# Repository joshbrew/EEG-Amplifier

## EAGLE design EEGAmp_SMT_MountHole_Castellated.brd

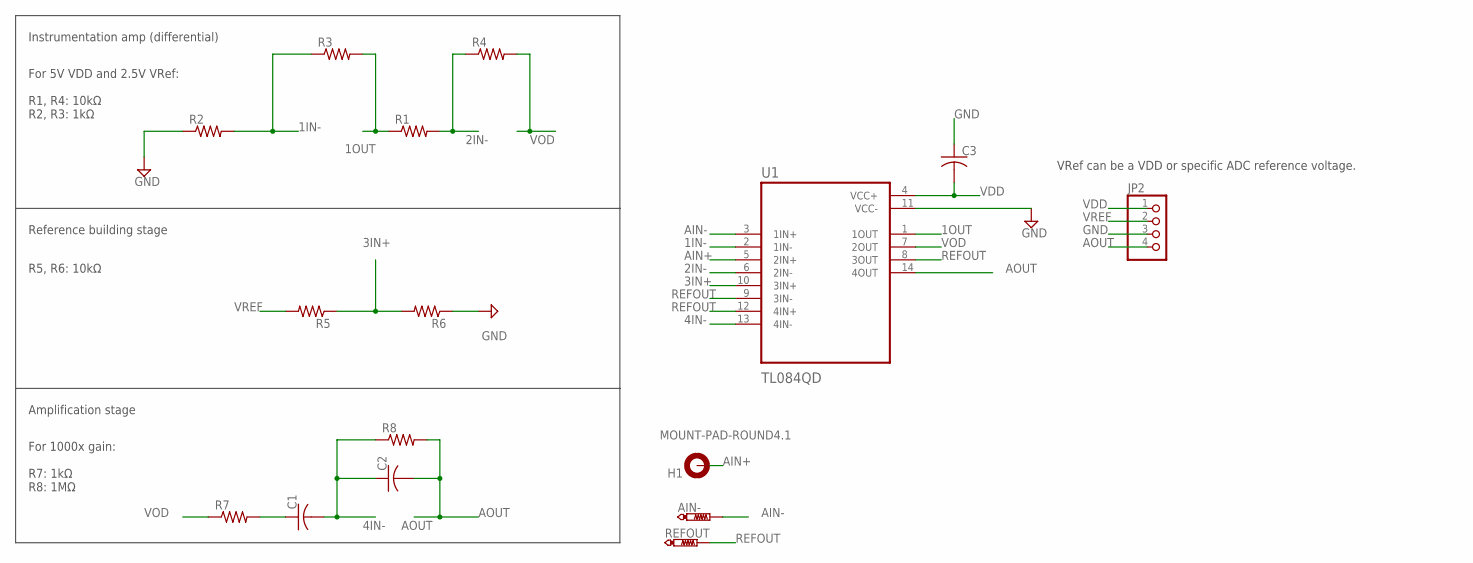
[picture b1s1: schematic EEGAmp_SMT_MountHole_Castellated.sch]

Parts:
AIN-: PTR1PAD1-17; P1-17
C1, C2, C3: C-USC0402; C0402
H1: MOUNT-PAD-ROUND4.1; 4,1-PAD
JP2: PINHD-1X4; 1X04
R1, R2, R3, R4, R5, R6, R7, R8: R-US_R0402; R0402
REFOUT: PTR1PAD1-17; P1-17
U1: TL084QD; SOIC127P600X175-14N

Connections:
1IN-: R2.2, R3.1, U1.2 (1IN-)
1OUT: R1.1, R3.2, U1.1 (1OUT)
2IN-: R1.2, R4.1, U1.6 (2IN-)
3IN+: R5.1, R6.2, U1.10 (3IN+)
4IN-: C1.2, C2.1, R8.1, U1.13 (4IN-)
AIN+: H1.B4,1, U1.5 (2IN+)
AIN-: AIN-.TP, U1.3 (1IN+)
AOUT: C2.2, JP2.4, R8.2, U1.14 (4OUT)
GND: C3.1, JP2.3, R2.1, R6.1, U1.11 (VCC-)
unnamed: C1.1, R7.2
REFOUT: REFOUT.TP, U1.8 (3OUT), U1.9 (3IN-), U1.12 (4IN+)
VDD: C3.2, JP2.1, U1.4 (VCC+)
VOD: R4.2, R7.1, U1.7 (2OUT)
VREF: JP2.2, R5.2

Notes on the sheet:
Instrumentation amp (differential)
Reference building stage
Amplification stage
For 5V VDD and 2.5V VRef: R1, R4: 10kΩ R2, R3: 1kΩ
R5, R6: 10kΩ
For 1000x gain: R7: 1kΩ R8: 1MΩ
VRef can be a VDD or specific ADC reference voltage.

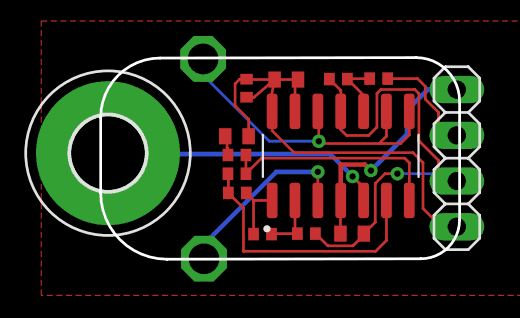
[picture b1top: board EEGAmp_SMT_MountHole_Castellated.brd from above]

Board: 2 copper layers, 19.9 x 11.2 mm, 16 parts (0 on the bottom side), 14 nets.

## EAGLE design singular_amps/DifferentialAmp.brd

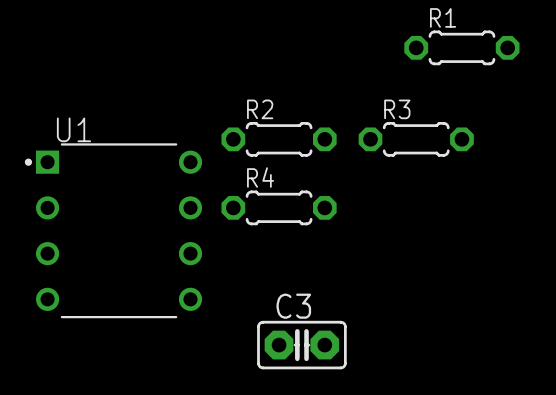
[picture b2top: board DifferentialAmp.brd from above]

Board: 2 copper layers, 6 parts (0 on the bottom side), 5 nets, no tracks yet.

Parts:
C3: C2.5-2
R1, R2, R3, R4: 0204/5
U1: TL082CP; DIP794W45P254L959H508Q8

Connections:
1IN-: R2.2, R3.1, U1.5
1OUT: R1.1, R3.2, U1.1
2IN-: R1.2, R4.1, U1.6
GND: C3.1, R2.1
VOD: R4.2, U1.7

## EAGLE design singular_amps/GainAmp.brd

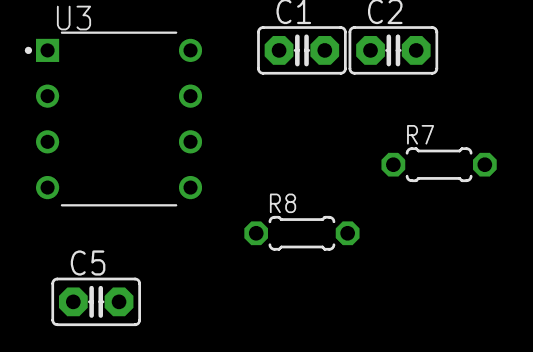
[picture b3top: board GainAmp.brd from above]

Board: 2 copper layers, 6 parts (0 on the bottom side), 3 nets, no tracks yet.

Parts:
C1, C2, C5: C2.5-2
R7, R8: 0204/5
U3: TL081CP; DIP794W45P254L959H508Q8

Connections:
4IN-: C1.2, C2.1, R8.1, U3.2
AOUT: C2.2, R8.2, U3.6
unnamed: C1.1, R7.2

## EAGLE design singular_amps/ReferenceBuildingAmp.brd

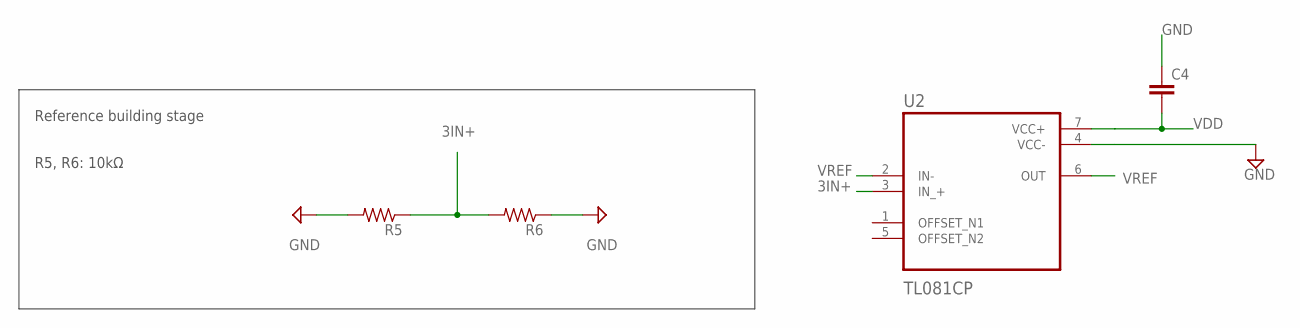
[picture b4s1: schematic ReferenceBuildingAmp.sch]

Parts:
C4: C2.5/2; C2.5-2
R5, R6: R-US_0204/5; 0204/5
U2: TL081CP; DIP794W45P254L959H508Q8

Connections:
3IN+: R5.1, R6.2, U2.3 (IN_+)
GND: C4.1, R5.2, R6.1
VDD: C4.2
VREF: U2.2 (IN-), U2.6 (OUT)

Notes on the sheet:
Reference building stage
R5, R6: 10kΩ

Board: 2 copper layers, 4 parts (0 on the bottom side), 3 nets, no tracks yet.
